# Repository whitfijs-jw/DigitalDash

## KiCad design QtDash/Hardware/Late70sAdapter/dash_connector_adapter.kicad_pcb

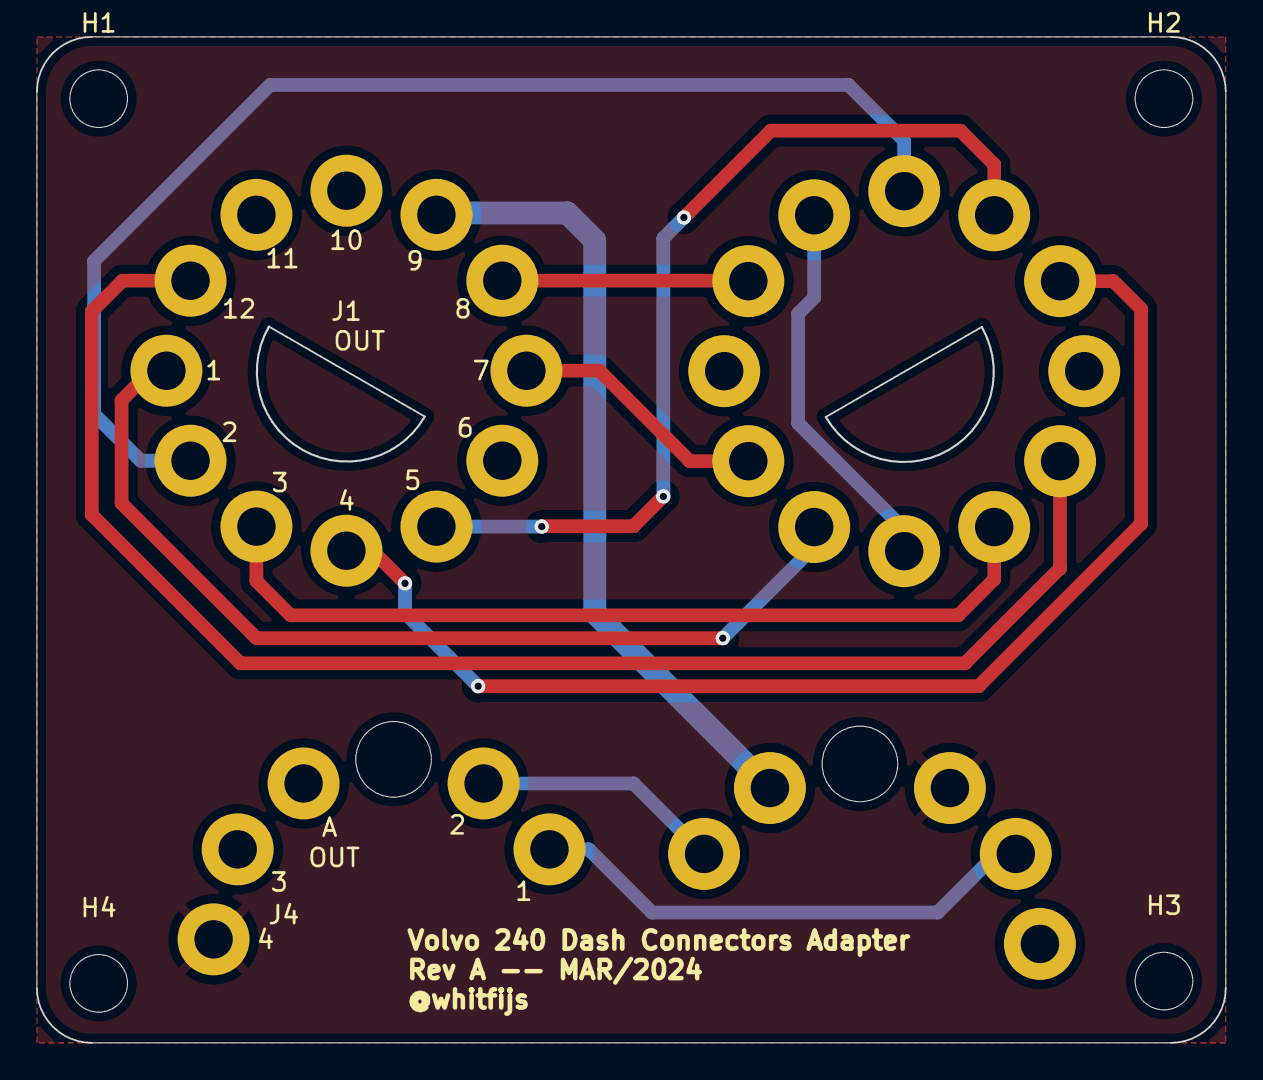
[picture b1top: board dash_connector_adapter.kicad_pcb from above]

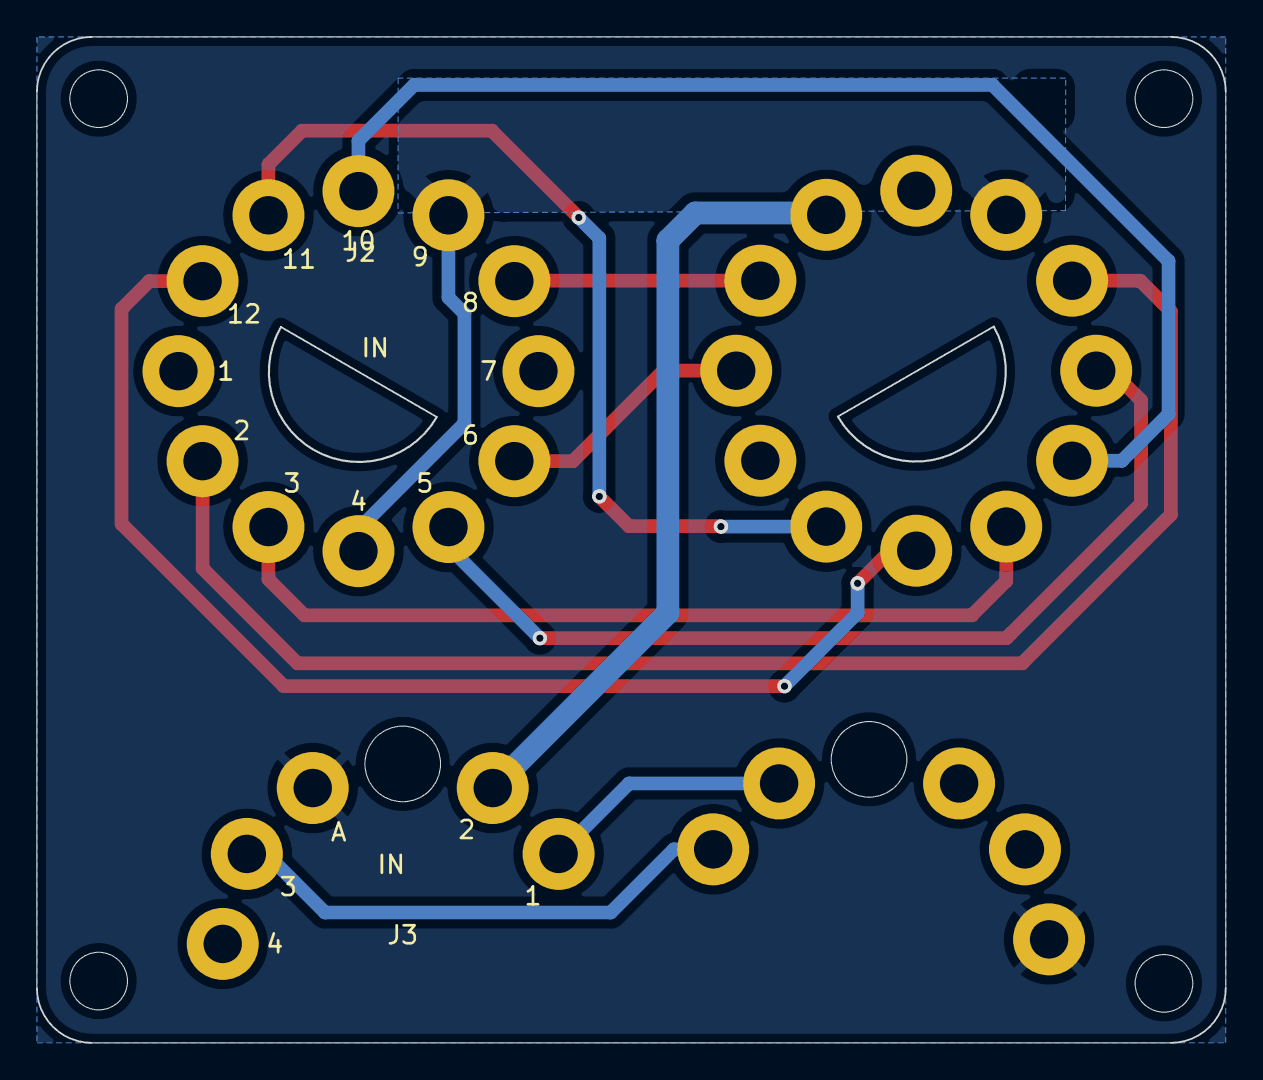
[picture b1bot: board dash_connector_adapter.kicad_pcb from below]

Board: 2 copper layers, 66.0 x 55.9 mm, 8 parts (2 on the bottom side), 13 nets.

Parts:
H1, H2, H3, H4: MountingHole; MountingHole_3.2mm_M3
J1, J2: CONN_31; VOLVO_CONN_31
J3, J4: CONN_32; VOLVO_CONN_32

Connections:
/12V_FUSE_8: J1.9, J3.2
/BLINKER_LEFT: J1.8, J2.8
/BLINKER_RIGHT: J1.7, J2.6
/BRAKE_FAILURE: J1.1, J2.5
/BULB_FAILURE: J1.12, J2.2
/CHARGING_D+: J1.11, J2.4, J2.9
/COOLANT_TEMP: J1.2, J2.10
/FUEL_LEVEL_SENDER: J3.4, J4.1
/GND: J3.A, J4.4
/HIGH_BEAM: J1.3, J2.3
/OD_LAMP: J1.4, J2.12
/OIL_LAMP: J1.5, J2.11
/PARKING_BRAKE: J3.1, J4.2

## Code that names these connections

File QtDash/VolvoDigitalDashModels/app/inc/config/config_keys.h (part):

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    static constexpr char USER_INPUT_GROUP[] = "user_inputs";

    // expected sensor keys
    static constexpr char COOLANT_TEMP_KEY[] = "coolant_temp";
    static constexpr char FUEL_LEVEL_KEY[] = "fuel_level";
    static constexpr char OIL_PRESSURE_KEY[] = "oil_pressure";
    static constexpr char OIL_TEMP_KEY[] = "oil_temp";
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    // expected dash light keys
    static constexpr char ACTIVE_LOW[] = "active_low";
    static constexpr char OIL_PRESSURE_SW_KEY[] = "oil_pressure_sw";
    static constexpr char OD_LAMP_KEY[] = "od_lamp";
    static constexpr char HIGH_BEAM_KEY[] = "high_beam";
    static constexpr char BRAKE_FAILURE_KEY[] = "brake_failure";
    static constexpr char BULB_FAILURE_KEY[] = "bulb_failure";
    static constexpr char CHARGING_LIGHT_KEY[] = "charging";
    static constexpr char BLINKER_LEFT_KEY[] = "blinker_left";
    static constexpr char BLINKER_RIGHT_KEY[] = "blinker_right";
    static constexpr char OD_LAMP_AUTO[] = "od_lamp_auto";
    static constexpr char CHECK_ENGINE_KEY[] = "check_engine";
    static constexpr char PARKING_BRAKE_KEY[] = "parking_brake";
    static constexpr char CONN_32_PIN3[] = "conn_32_pin3";

    // expected user input keys
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    static constexpr qreal DEFAULT_BOOST_GAUGE_MIN_BAR = -1.0;
    static constexpr qreal DEFAULT_BOOST_GAUGE_MAX_BAR = 1.5;
    //coolant temp gauge configs
    static constexpr char COOLANT_TEMP_GAUGE_GROUP[] = "coolant_temp";
    static constexpr qreal DEFAULT_COOLANT_TEMP_GAUGE_MIN_F = 120.0;
    static constexpr qreal DEFAULT_COOLANT_TEMP_GAUGE_MAX_F = 250.0;

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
